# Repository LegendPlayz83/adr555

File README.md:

# adr555
This is my 555 timer blinky project made in KiCad

PCB:

Schematic:

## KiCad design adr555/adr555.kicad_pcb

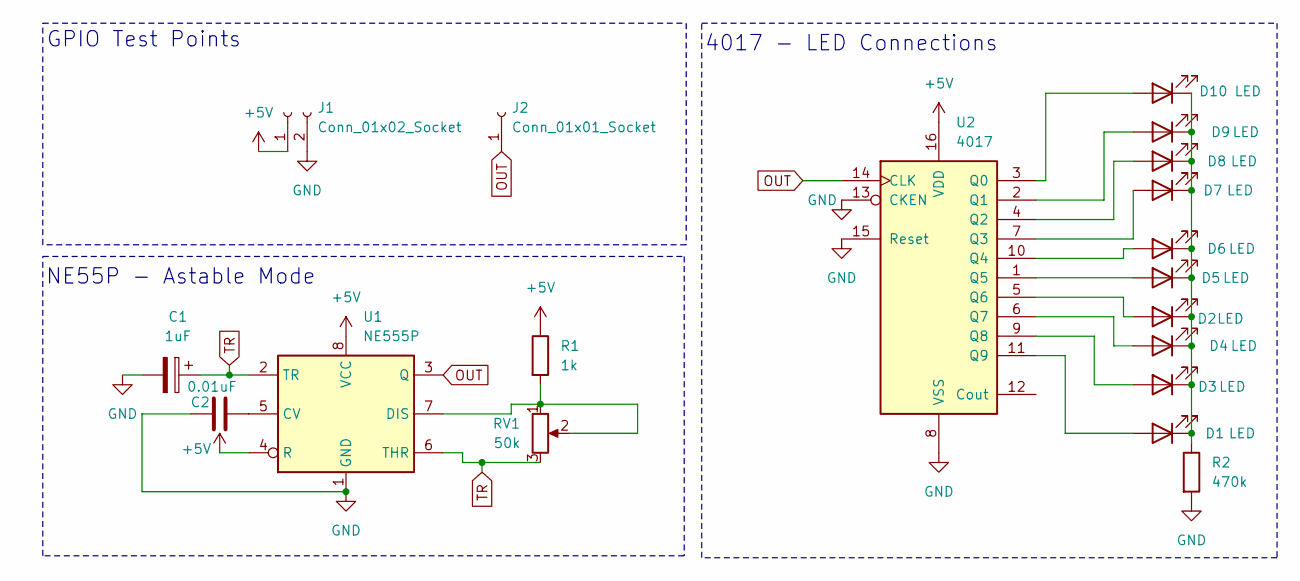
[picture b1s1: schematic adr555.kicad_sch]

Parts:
C1: 1uF; CP_Radial_D5.0mm_P2.00mm
C2: 0.01uF; C_Disc_D7.5mm_W2.5mm_P5.00mm
D1, D2, D3, D4, D5, D6, D7, D8, D9, D10: LED; LED_D3.0mm
J1: Conn_01x02_Socket; PinHeader_1x02_P2.54mm_Vertical
J2: Conn_01x01_Socket; PinHeader_1x01_P2.54mm_Vertical
R1: 1k; R_Axial_DIN0207_L6.3mm_D2.5mm_P7.62mm_Horizontal
R2: 470k; R_Axial_DIN0207_L6.3mm_D2.5mm_P7.62mm_Horizontal
RV1: 50k; Potentiometer_Vishay_T93XA_Horizontal
U1: NE555P; DIP-8_W7.62mm
U2: 4017; N16

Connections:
+5V: J1.1, R1.1, U1.4 (R), U1.8 (VCC), U2.16 (VDD)
GND: C1.2, C2.1, J1.2, R2.2, U1.1 (GND), U2.8 (VSS), U2.13 (CKEN), U2.15 (Reset)
unnamed: D1.2 (A), U2.11 (Q9)
unnamed: D1.1 (K), D2.1 (K), D3.1 (K), D4.1 (K), D5.1 (K), D6.1 (K), D7.1 (K), D8.1 (K), D9.1 (K), D10.1 (K), R2.1
unnamed: D2.2 (A), U2.5 (Q6)
unnamed: D3.2 (A), U2.9 (Q8)
unnamed: D4.2 (A), U2.6 (Q7)
unnamed: D5.2 (A), U2.1 (Q5)
unnamed: D6.2 (A), U2.10 (Q4)
unnamed: D7.2 (A), U2.7 (Q3)
unnamed: D8.2 (A), U2.4 (Q2)
unnamed: D9.2 (A), U2.2 (Q1)
unnamed: D10.2 (A), U2.3 (Q0)
unnamed: C2.2, U1.5 (CV)
unnamed: R1.2, RV1.1, RV1.2, U1.7 (DIS)
OUT: J2.1, U1.3 (Q), U2.14 (CLK)
TR: C1.1, RV1.3, U1.2 (TR), U1.6 (THR)

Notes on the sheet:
NE55P - Astable Mode
4017 - LED Connections
GPIO Test Points

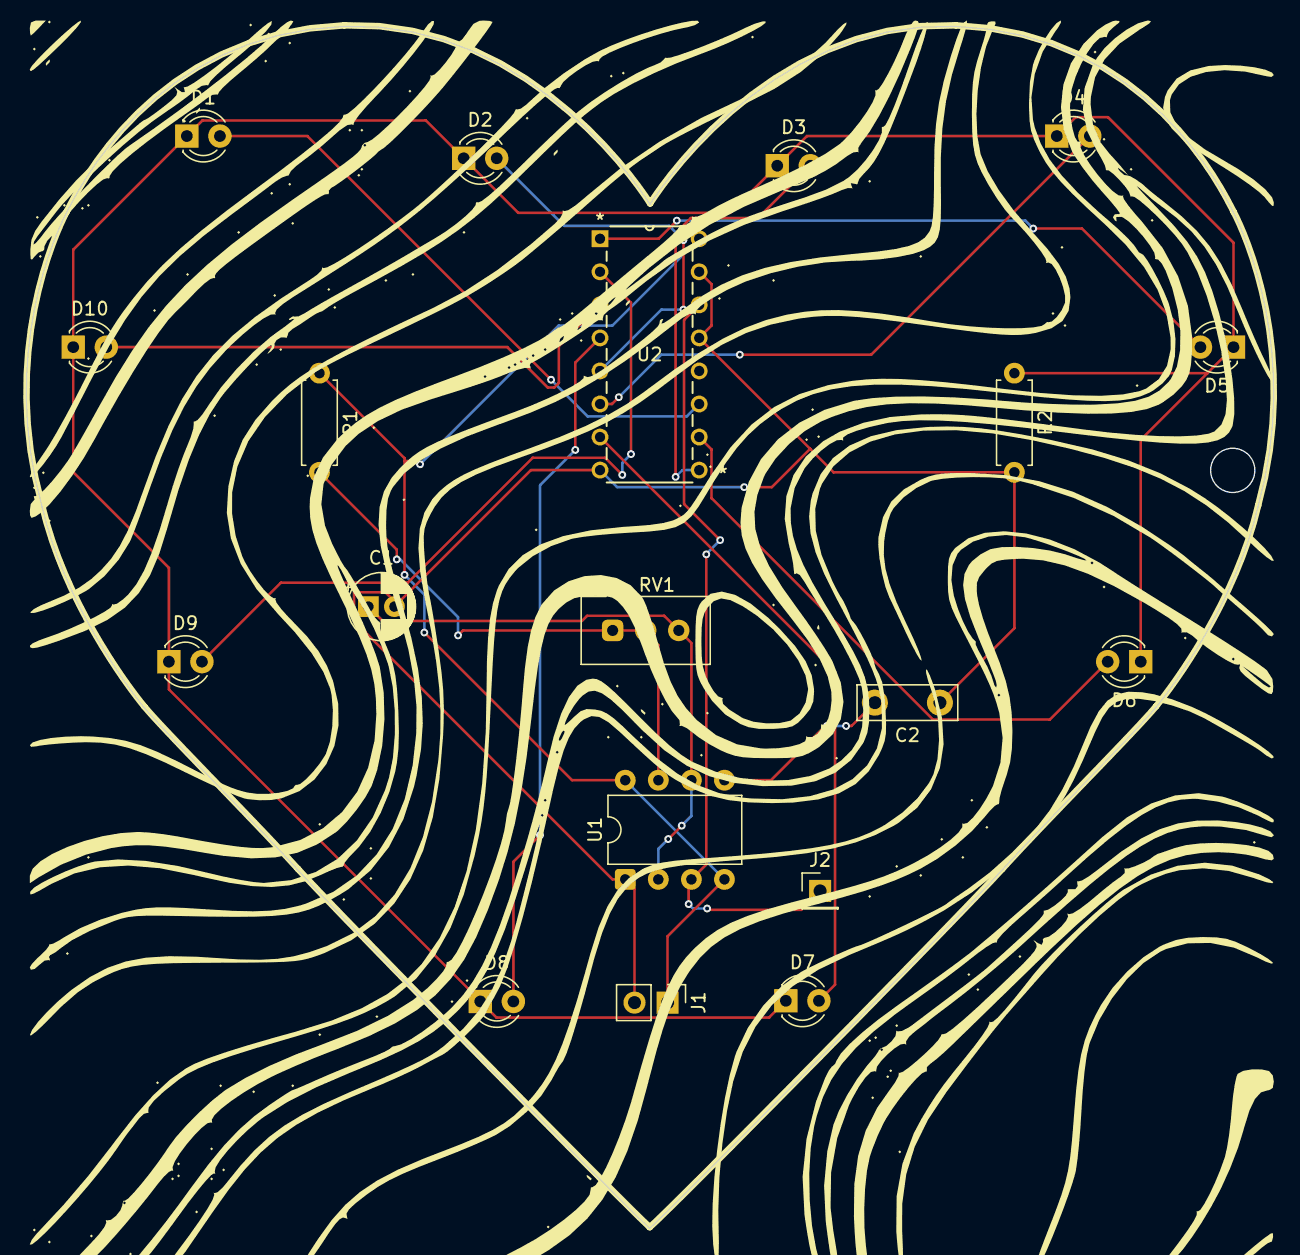
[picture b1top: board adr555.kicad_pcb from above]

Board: 2 copper layers, 95.8 x 92.4 mm, 19 parts (0 on the bottom side), 17 nets.

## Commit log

2026-04-25 Enhance README with project details and images
    Updated project description and added images for PCB and schematic.
